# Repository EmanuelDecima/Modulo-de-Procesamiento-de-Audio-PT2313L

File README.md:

# Módulo de Procesamiento de Audio PT2313L
Módulo estéreo de control de volumen, tono, balance y loudness basado en el integrado PT2313L. Diseñado para aplicaciones de audio Hi-Fi y sistemas de sonido personalizados.

## Características
- Control digital de volumen, tono, balance y loudness mediante bus I²C.
- Entradas de audio estéreo con selección de canal.
- Alimentación simple de 9–12 V DC.
- Pines de control compatibles con microcontroladores (Arduino, STM32, ESP32, etc.).
- PCB de simple faz, tamaño compacto (100 mm × 50 mm).
- Boneras para alimentación y salidas de audio
- Conector JST para entradas de audio
- Conector de 4 pines para comunicación mediante bus I²C.

## Esquema y PCB

## Documentación técnica
El módulo está basado en el integrado **PT2313L**, un procesador de audio con control digital I²C.  
Las señales de audio ingresan a través de conectores JST y pasan por la etapa de selección y control del PT2313L antes de salir hacia el amplificador.  
Los niveles de volumen, balance y tono son programables por software.

## Requisitos
- Controlador I²C (Arduino, STM32, ESP32, Raspberry Pi, etc.)
- Fuente de alimentación regulada 9–12 V DC
- Señal de audio de nivel de línea

## Compatibilidad
Probado con:
- Arduino Nano / UNO
- STM32F103C8 ("Blue Pill")
- ESP32-WROOM

## Autor
Diseñado por Emanuel Décima  
Contacto: emanueldecima3@gmail.com  
Noviembre 2025

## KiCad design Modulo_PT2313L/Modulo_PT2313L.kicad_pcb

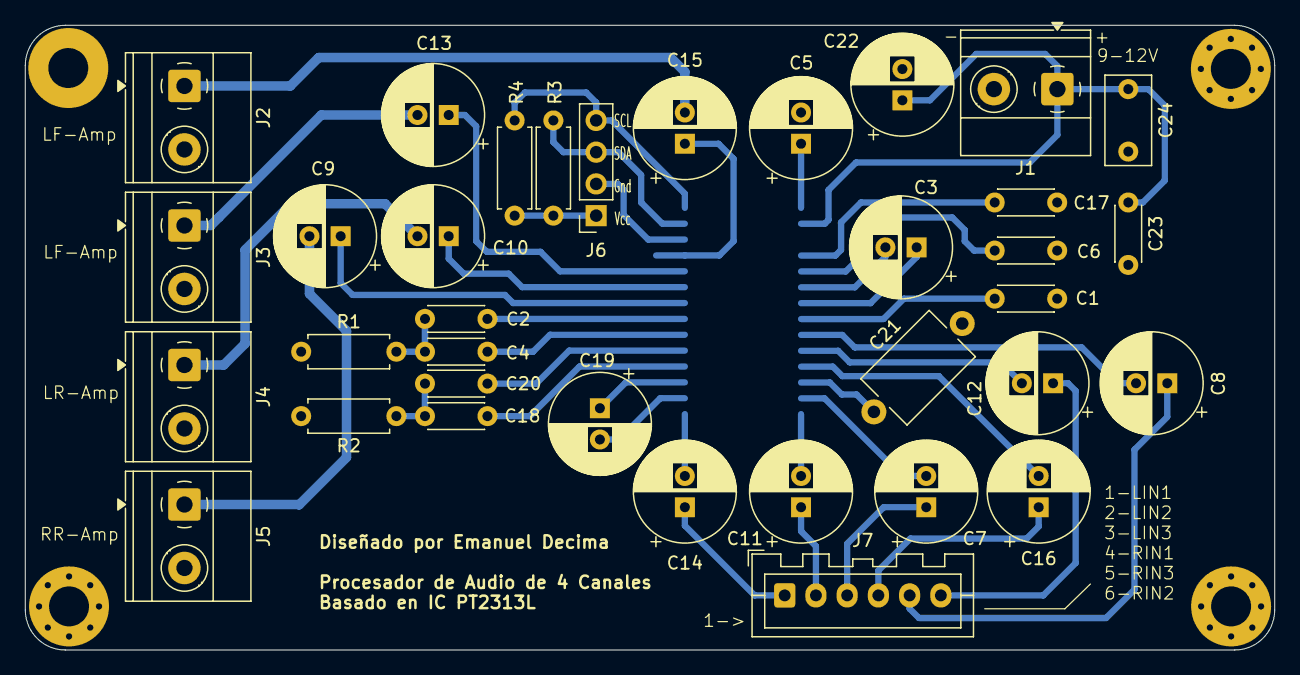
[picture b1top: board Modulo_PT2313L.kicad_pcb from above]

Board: 2 copper layers, 100.0 x 50.0 mm, 36 parts (1 on the bottom side), 41 nets.

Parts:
C1, C2, C4, C18, C20, C23: 100nF; C_Disc_D4.3mm_W1.9mm_P5.00mm
C3, C7, C8, C9, C10, C11, C12, C13, C14, C15, C16, C19, C22: 2.2uF; CP_Radial_D8.0mm_P2.50mm
C5: 22uF; CP_Radial_D8.0mm_P2.50mm
C6, C17: 2,7nF; C_Disc_D4.3mm_W1.9mm_P5.00mm
C21: 100nF; C_Disc_D7.5mm_W5.0mm_P10.00mm
C24: 4,7nF; C_Rect_L7.0mm_W3.5mm_P5.00mm
J1: Power 9V; TerminalBlock_Phoenix_MKDS-1,5-2-5.08_1x02_P5.08mm_Horizont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
J2: LF_Amp; TerminalBlock_Phoenix_MKDS-1,5-2-5.08_1x02_P5.08mm_Horizont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
J3: RF_Amp; TerminalBlock_Phoenix_MKDS-1,5-2-5.08_1x02_P5.08mm_Horizont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
J4: LR_Amp; TerminalBlock_Phoenix_MKDS-1,5-2-5.08_1x02_P5.08mm_Horizont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
J5: RR_Amp; TerminalBlock_Phoenix_MKDS-1,5-2-5.08_1x02_P5.08mm_Horizont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
J6: I2C_Conn; PinSocket_1x04_P2.54mm_Vertical
J7: Inputs; JST_XA_B06B-XASK-1_1x06_P2.50mm_Vertical
R1, R2, R3, R4: 5K6; R_Axial_DIN0207_L6.3mm_D2.5mm_P7.62mm_Horizontal
U1: PT2313; SOIC-28W_7.5x17.9mm_P1.27mm

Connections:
+3V3: J6.1, R3.1, R4.1
/LIN1: C14.1, J7.1
/LIN2: C11.1, J7.2
/LIN3: C7.1, J7.3
/RIN1: C16.1, J7.4
/RIN2: C12.1, J7.6
/RIN3: C8.1, J7.5
GND: C1.2, C5.2, C6.2, C17.2, C21.2, C22.2, C23.2, C24.2, J1.2, J2.2, J3.2, J4.2, J5.2, R1.2, R2.2, U1.3 (AGND)
GNDD: J6.2, U1.26 (DGND)
unnamed: C2.2, C4.2, R1.1
unnamed: C18.2, C20.2, R2.1
unnamed: C15.2, J2.1
unnamed: C13.2, J3.1
unnamed: C10.2, J4.1
unnamed: C9.2, J5.1
unnamed: J6.3, R3.2, U1.27 (DATA)
unnamed: J6.4, R4.2, U1.28 (CLK)
unnamed: C18.1, U1.18 (BIN_L)
unnamed: C4.1, U1.20 (BIN_R)
unnamed: C20.1, U1.19 (BOUT_L)
unnamed: C2.1, U1.21 (BOUT_R)
unnamed: C15.1, U1.25 (LFOUT)
unnamed: C14.2, U1.15 (LIN1)
unnamed: C11.2, U1.14 (LIN2)
unnamed: C7.2, U1.13 (LIN3)
unnamed: C19.2, U1.16 (LIN)
unnamed: C21.1, U1.12 (LOUD_L)
unnamed: C1.1, U1.8 (LOUD_R)
unnamed: C19.1, U1.17 (LOUT)
unnamed: C10.1, U1.23 (LROUT)
unnamed: C5.1, U1.1 (REF)
unnamed: C13.1, U1.24 (RFOUT)
unnamed: C16.2, U1.11 (RIN1)
unnamed: C12.2, U1.10 (RIN2)
unnamed: C8.2, U1.9 (RIN3)
unnamed: C3.2, U1.6 (RIN)
unnamed: C3.1, U1.7 (ROUT)
unnamed: C9.1, U1.22 (RROUT)
unnamed: C17.1, U1.4 (TREB_L)
unnamed: C6.1, U1.5 (TREB_R)
VDD: C22.1, C23.1, C24.1, J1.1, U1.2 (VDD)

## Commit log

2026-02-26 Cambios en la Serigrafia
2026-03-24 readme actualizado
